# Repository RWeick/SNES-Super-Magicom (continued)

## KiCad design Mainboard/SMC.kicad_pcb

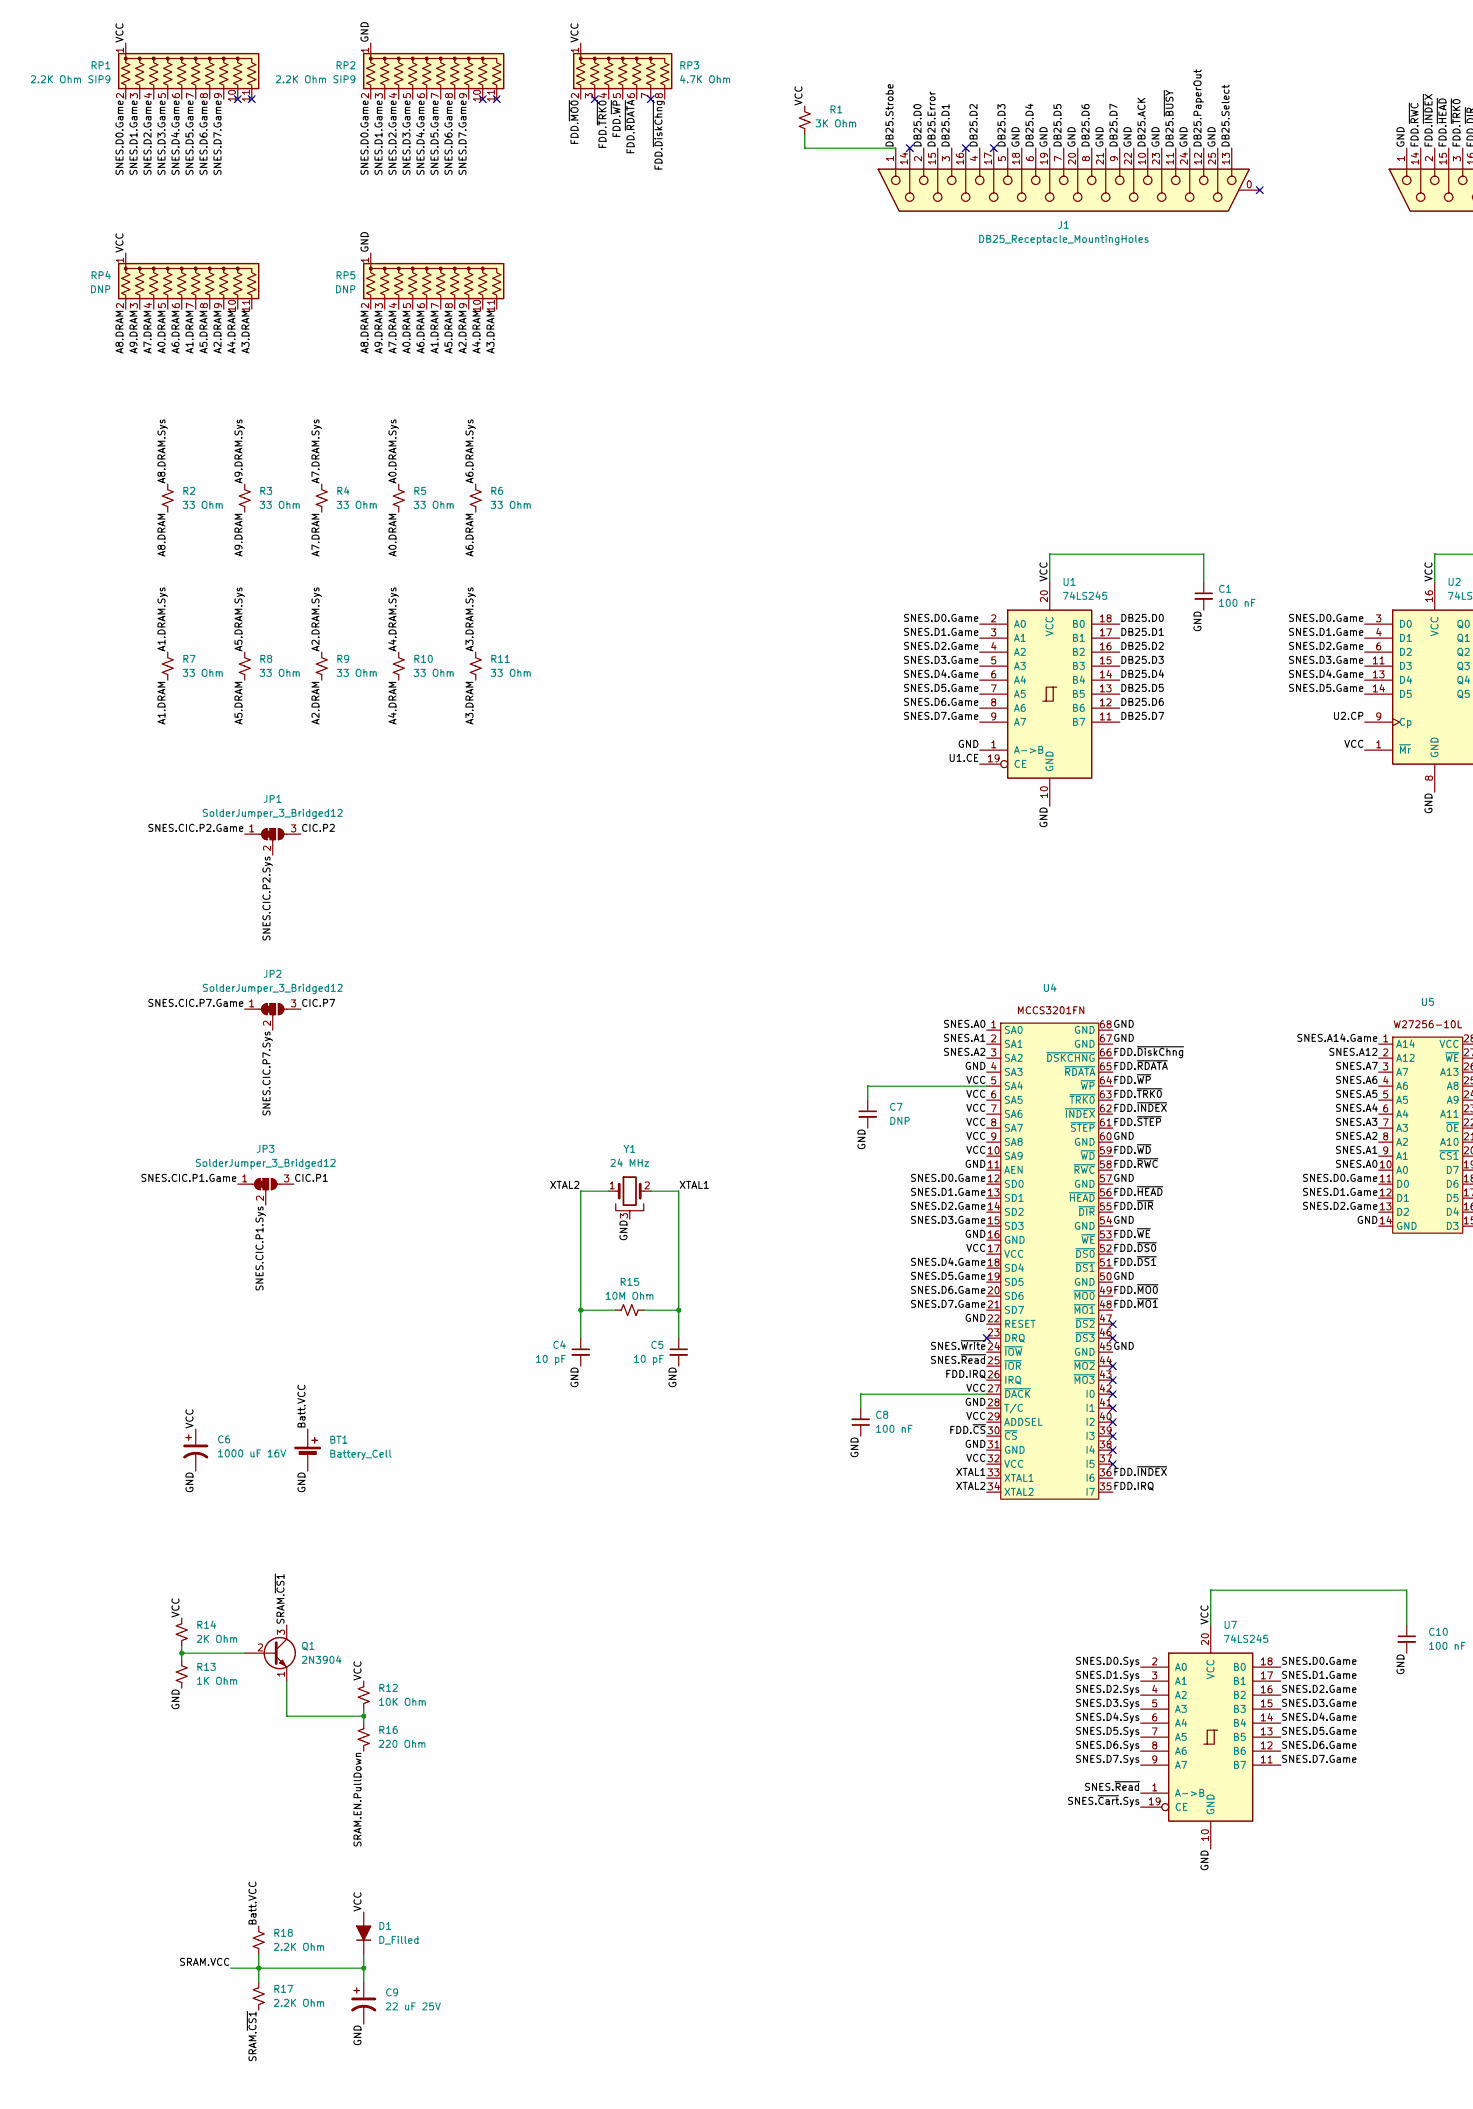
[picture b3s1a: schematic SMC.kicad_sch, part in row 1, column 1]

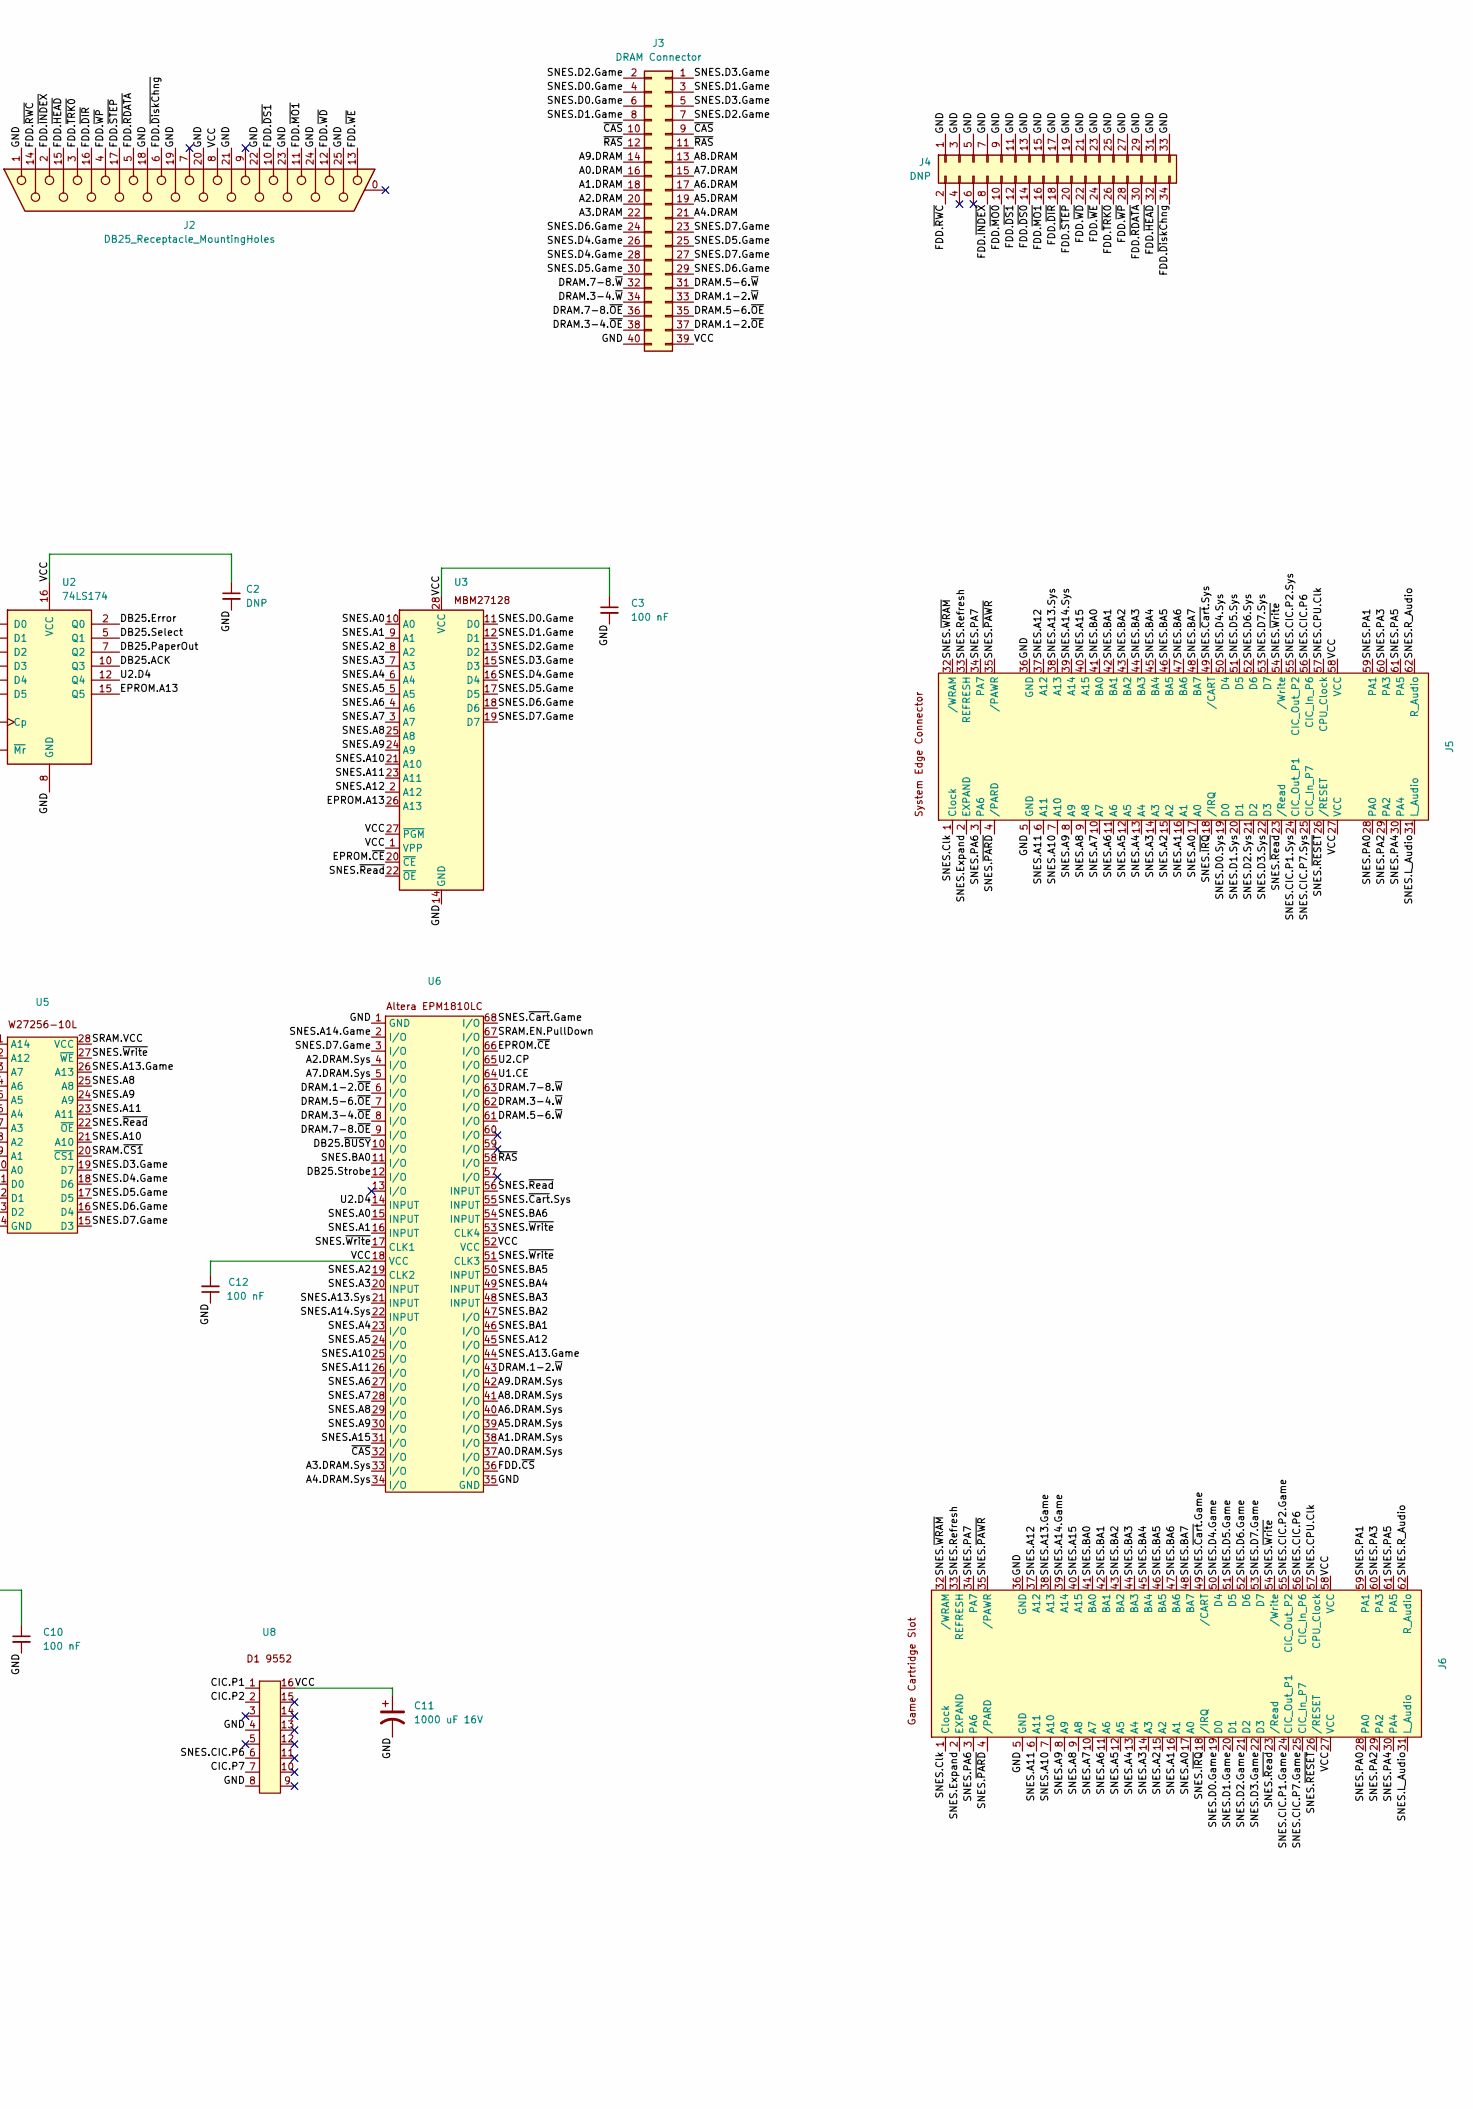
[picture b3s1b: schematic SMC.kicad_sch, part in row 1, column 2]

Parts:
BT1: Battery_Cell; Battery
C1, C3, C8, C10, C12: 100 nF; C_Disc_D4.3mm_W1.9mm_P5.00mm
C2, C7: DNP; C_Disc_D4.3mm_W1.9mm_P5.00mm
C4, C5: 10 pF; C_Disc_D4.3mm_W1.9mm_P5.00mm
C6, C11: 1000 uF 16V; C_Disc_D4.3mm_W1.9mm_P5.00mm
C9: 22 uF 25V; C_Disc_D4.3mm_W1.9mm_P5.00mm
D1: D_Filled; D_DO-15_P10.16mm_Horizontal
J1, J2: DB25_Receptacle_MountingHoles; DSUB-25_Female_Horizontal_P2.77x2.84mm_EdgePinOffset4.94mm_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
J3: DRAM Connector; PinHeader_2x20_P2.54mm_Vertical
J4: DNP; PinHeader_2x17_P2.54mm_Vertical
J5: SNES Connector Slot
J6: SNES Cartridge Slot
JP1, JP2, JP3: SolderJumper_3_Bridged12; SolderJumper-3_P1.3mm_Open_RoundedPad1.0x1.5mm_NumberLabels
Q1: 2N3904; TO-92_Wide
R1: 3K Ohm; R_Axial_DIN0207_L6.3mm_D2.5mm_P10.16mm_Horizontal
R2, R3, R4, R5, R6, R7, R8, R9, R10, R11: 33 Ohm; R_Axial_DIN0207_L6.3mm_D2.5mm_P10.16mm_Horizontal
R12: 10K Ohm; R_Axial_DIN0207_L6.3mm_D2.5mm_P10.16mm_Horizontal
R13: 1K Ohm; R_Axial_DIN0207_L6.3mm_D2.5mm_P10.16mm_Horizontal
R14: 2K Ohm; R_Axial_DIN0207_L6.3mm_D2.5mm_P10.16mm_Horizontal
R15: 10M Ohm; R_Axial_DIN0207_L6.3mm_D2.5mm_P10.16mm_Horizontal
R16: 220 Ohm; R_Axial_DIN0207_L6.3mm_D2.5mm_P10.16mm_Horizontal
R17, R18: 2.2K Ohm; R_Axial_DIN0207_L6.3mm_D2.5mm_P10.16mm_Horizontal
RP1, RP2: 2.2K Ohm SIP9; PinHeader_1x11_P2.54mm_Vertical
RP3: 4.7K Ohm; PinHeader_1x08_P2.54mm_Vertical
RP4, RP5: DNP; PinHeader_1x11_P2.54mm_Vertical
U1, U7: 74LS245; DIP-20_W7.62mm
U2: 74LS174; DIP-16_W7.62mm
U3: 27128; DIP-28_W15.24mm
U4, U6: PLCC-68_THT-Socket
U5: DIP-28_W15.24mm
U8: DIP-16_W7.62mm
Y1: 24 MHz; Crystal_HC18-U_Horizontal_1EP_style2

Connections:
/A0.DRAM: J3.16, R5.1, RP4.5 (R4), RP5.5 (R4)
/A0.DRAM.Sys: R5.2, U6.37 (I/O)
/A1.DRAM: J3.18, R7.1, RP4.7 (R6), RP5.7 (R6)
/A1.DRAM.Sys: R7.2, U6.38 (I/O)
/A2.DRAM: J3.20, R9.1, RP4.9 (R8), RP5.9 (R8)
/A2.DRAM.Sys: R9.2, U6.4 (I/O)
/A3.DRAM: J3.22, R11.1, RP4.11 (R10), RP5.11 (R10)
/A3.DRAM.Sys: R11.2, U6.33 (I/O)
/A4.DRAM: J3.21, R10.1, RP4.10 (R9), RP5.10 (R9)
/A4.DRAM.Sys: R10.2, U6.34 (I/O)
/A5.DRAM: J3.19, R8.1, RP4.8 (R7), RP5.8 (R7)
/A5.DRAM.Sys: R8.2, U6.39 (I/O)
/A6.DRAM: J3.17, R6.1, RP4.6 (R5), RP5.6 (R5)
/A6.DRAM.Sys: R6.2, U6.40 (I/O)
/A7.DRAM: J3.15, R4.1, RP4.4 (R3), RP5.4 (R3)
/A7.DRAM.Sys: R4.2, U6.5 (I/O)
/A8.DRAM: J3.13, R2.1, RP4.2 (R1), RP5.2 (R1)
/A8.DRAM.Sys: R2.2, U6.41 (I/O)
/A9.DRAM: J3.14, R3.1, RP4.3 (R2), RP5.3 (R2)
/A9.DRAM.Sys: R3.2, U6.42 (I/O)
/Batt.VCC: BT1.1 (+), R18.2
/CIC.P1: JP3.3 (B), U8.1
/CIC.P2: JP1.3 (B), U8.2
/CIC.P7: JP2.3 (B), U8.7
/DB25.ACK: J1.10, U2.10 (Q3)
/DB25.D0: J1.2, U1.18 (B0)
/DB25.D1: J1.3, U1.17 (B1)
/DB25.D2: J1.4, U1.16 (B2)
/DB25.D3: J1.5, U1.15 (B3)
/DB25.D4: J1.6, U1.14 (B4)
/DB25.D5: J1.7, U1.13 (B5)
/DB25.D6: J1.8, U1.12 (B6)
/DB25.D7: J1.9, U1.11 (B7)
/DB25.Error: J1.15, U2.2 (Q0)
/DB25.PaperOut: J1.12, U2.7 (Q2)
/DB25.Select: J1.13, U2.5 (Q1)
/DB25.Strobe: J1.1, R1.2, U6.12 (I/O)
/DB25.~BUSY: J1.11, U6.10 (I/O)
/DRAM.1-2.~OE: J3.37, U6.6 (I/O)
/DRAM.1-2.~W: J3.33, U6.43 (I/O)
/DRAM.3-4.~OE: J3.38, U6.8 (I/O)
/DRAM.3-4.~W: J3.34, U6.62 (I/O)
/DRAM.5-6.~OE: J3.35, U6.7 (I/O)
/DRAM.5-6.~W: J3.31, U6.61 (I/O)
/DRAM.7-8.~OE: J3.36, U6.9 (I/O)
/DRAM.7-8.~W: J3.32, U6.63 (I/O)
/EPROM.A13: U2.15 (Q5), U3.26 (A13)
/EPROM.~CE: U3.20 (~CE), U6.66 (I/O)
/FDD.IRQ: U4.26 (IRQ), U4.35 (I7)
/FDD.~CS: U4.30 (~CS), U6.36 (I/O)
/FDD.~DIR: J2.16, J4.18, U4.55 (~DIR)
/FDD.~DS0: J4.14, U4.52 (~DS0)
/FDD.~DS1: J2.10, J4.12, U4.51 (~DS1)
/FDD.~DiskChng: J2.6, J4.34, RP3.8 (R7), U4.66 (~DSKCHNG)
/FDD.~HEAD: J2.15, J4.32, U4.56 (~HEAD)
/FDD.~INDEX: J2.2, J4.8, U4.36 (I6), U4.62 (~INDEX)
/FDD.~MO0: J4.10, RP3.2 (R1), U4.49 (~MO0)
/FDD.~MO1: J2.11, J4.16, U4.48 (~MO1)
/FDD.~RDATA: J2.5, J4.30, RP3.6 (R5), U4.65 (~RDATA)
/FDD.~RWC: J2.14, J4.2, U4.58 (~RWC)
/FDD.~STEP: J2.17, J4.20, U4.61 (~STEP)
/FDD.~TRK0: J2.3, J4.26, RP3.4 (R3), U4.63 (~TRK0)
/FDD.~WD: J2.12, J4.22, U4.59 (~WD)
/FDD.~WE: J2.13, J4.24, U4.53 (~WE)
/FDD.~WP: J2.4, J4.28, RP3.5 (R4), U4.64 (~WP)
/GND: BT1.2 (-), C1.2, C2.2, C3.2, C4.2, C5.2, C6.2, C7.2, C8.1, C9.2, C10.2, C11.2, C12.1, J1.18, J1.19, J1.20, J1.21, J1.22, J1.23, J1.24, J1.25, J2.1, J2.18, J2.19, J2.20, J2.21, J2.22, J2.23, J2.24, J2.25, J3.40, J4.1, J4.3, J4.5, J4.7, J4.9, J4.11, J4.13, J4.15, J4.17, J4.19, J4.21, J4.23, J4.25, J4.27, J4.29, J4.31, J4.33, J5.5 (GND), J5.36 (GND), J6.5 (GND), J6.36 (GND), R13.1, RP2.1 (common), RP5.1 (common), U1.1 (A->B), U1.10 (GND), U2.8 (GND), U3.14 (GND), U4.4 (SA3), U4.11 (AEN), U4.16 (GND), U4.22 (RESET), U4.28 (T/C), U4.31 (GND), U4.45 (GND), U4.50 (GND), U4.54 (GND), U4.57 (GND), U4.60 (GND), U4.67 (GND), U4.68 (GND), U5.14 (GND), U6.1 (GND), U6.35 (GND), U7.10 (GND), U8.4, U8.8, Y1.3
/SNES.A0: J5.17 (A0), J6.17 (A0), U3.10 (A0), U4.1 (SA0), U5.10 (A0), U6.15 (INPUT)
/SNES.A1: J5.16 (A1), J6.16 (A1), U3.9 (A1), U4.2 (SA1), U5.9 (A1), U6.16 (INPUT)
/SNES.A2: J5.15 (A2), J6.15 (A2), U3.8 (A2), U4.3 (SA2), U5.8 (A2), U6.19 (CLK2)
/SNES.A3: J5.14 (A3), J6.14 (A3), U3.7 (A3), U5.7 (A3), U6.20 (INPUT)
/SNES.A4: J5.13 (A4), J6.13 (A4), U3.6 (A4), U5.6 (A4), U6.23 (I/O)
/SNES.A5: J5.12 (A5), J6.12 (A5), U3.5 (A5), U5.5 (A5), U6.24 (I/O)
/SNES.A6: J5.11 (A6), J6.11 (A6), U3.4 (A6), U5.4 (A6), U6.27 (I/O)
/SNES.A7: J5.10 (A7), J6.10 (A7), U3.3 (A7), U5.3 (A7), U6.28 (I/O)
/SNES.A8: J5.9 (A8), J6.9 (A8), U3.25 (A8), U5.25 (A8), U6.29 (I/O)
/SNES.A9: J5.8 (A9), J6.8 (A9), U3.24 (A9), U5.24 (A9), U6.30 (I/O)
/SNES.A10: J5.7 (A10), J6.7 (A10), U3.21 (A10), U5.21 (A10), U6.25 (I/O)
/SNES.A11: J5.6 (A11), J6.6 (A11), U3.23 (A11), U5.23 (A11), U6.26 (I/O)
/SNES.A12: J5.37 (A12), J6.37 (A12), U3.2 (A12), U5.2 (A12), U6.45 (I/O)
/SNES.A13.Game: J6.38 (A13), U5.26 (A13), U6.44 (I/O)
/SNES.A13.Sys: J5.38 (A13), U6.21 (INPUT)
/SNES.A14.Game: J6.39 (A14), U5.1 (A14), U6.2 (I/O)
/SNES.A14.Sys: J5.39 (A14), U6.22 (INPUT)
/SNES.A15: J5.40 (A15), J6.40 (A15), U6.31 (I/O)
/SNES.BA0: J5.41 (BA0), J6.41 (BA0), U6.11 (I/O)
/SNES.BA1: J5.42 (BA1), J6.42 (BA1), U6.46 (I/O)
/SNES.BA2: J5.43 (BA2), J6.43 (BA2), U6.47 (I/O)
/SNES.BA3: J5.44 (BA3), J6.44 (BA3), U6.48 (INPUT)
/SNES.BA4: J5.45 (BA4), J6.45 (BA4), U6.49 (INPUT)
/SNES.BA5: J5.46 (BA5), J6.46 (BA5), U6.50 (INPUT)
/SNES.BA6: J5.47 (BA6), J6.47 (BA6), U6.54 (INPUT)
/SNES.BA7: J5.48 (BA7), J6.48 (BA7)
/SNES.CIC.P1.Game: J6.24 (CIC_Out_P1), JP3.1 (A)
/SNES.CIC.P1.Sys: J5.24 (CIC_Out_P1), JP3.2 (C)
/SNES.CIC.P2.Game: J6.55 (CIC_Out_P2), JP1.1 (A)
/SNES.CIC.P2.Sys: J5.55 (CIC_Out_P2), JP1.2 (C)
/SNES.CIC.P6: J5.56 (CIC_In_P6), J6.56 (CIC_In_P6), U8.6
/SNES.CIC.P7.Game: J6.25 (CIC_In_P7), JP2.1 (A)
/SNES.CIC.P7.Sys: J5.25 (CIC_In_P7), JP2.2 (C)
/SNES.CPU.Clk: J5.57 (CPU_Clock), J6.57 (CPU_Clock)
/SNES.Clk: J5.1 (Clock), J6.1 (Clock)
/SNES.D0.Game: J3.4, J3.6, J6.19 (D0), RP1.2 (R1), RP2.2 (R1), U1.2 (A0), U2.3 (D0), U3.11 (D0), U4.12 (SD0), U5.11 (D0), U7.18 (B0)
/SNES.D0.Sys: J5.19 (D0), U7.2 (A0)
/SNES.D1.Game: J3.3, J3.8, J6.20 (D1), RP1.3 (R2), RP2.3 (R2), U1.3 (A1), U2.4 (D1), U3.12 (D1), U4.13 (SD1), U5.12 (D1), U7.17 (B1)
/SNES.D1.Sys: J5.20 (D1), U7.3 (A1)
/SNES.D2.Game: J3.2, J3.7, J6.21 (D2), RP1.4 (R3), RP2.4 (R3), U1.4 (A2), U2.6 (D2), U3.13 (D2), U4.14 (SD2), U5.13 (D2), U7.16 (B2)
/SNES.D2.Sys: J5.21 (D2), U7.4 (A2)
/SNES.D3.Game: J3.1, J3.5, J6.22 (D3), RP1.5 (R4), RP2.5 (R4), U1.5 (A3), U2.11 (D3), U3.15 (D3), U4.15 (SD3), U5.19 (D7), U7.15 (B3)
/SNES.D3.Sys: J5.22 (D3), U7.5 (A3)
/SNES.D4.Game: J3.26, J3.28, J6.50 (D4), RP1.6 (R5), RP2.6 (R5), U1.6 (A4), U2.13 (D4), U3.16 (D4), U4.18 (SD4), U5.18 (D6), U7.14 (B4)
/SNES.D4.Sys: J5.50 (D4), U7.6 (A4)
/SNES.D5.Game: J3.25, J3.30, J6.51 (D5), RP1.7 (R6), RP2.7 (R6), U1.7 (A5), U2.14 (D5), U3.17 (D5), U4.19 (SD5), U5.17 (D5), U7.13 (B5)
/SNES.D5.Sys: J5.51 (D5), U7.7 (A5)
/SNES.D6.Game: J3.24, J3.29, J6.52 (D6), RP1.8 (R7), RP2.8 (R7), U1.8 (A6), U3.18 (D6), U4.20 (SD6), U5.16 (D4), U7.12 (B6)
/SNES.D6.Sys: J5.52 (D6), U7.8 (A6)
/SNES.D7.Game: J3.23, J3.27, J6.53 (D7), RP1.9 (R8), RP2.9 (R8), U1.9 (A7), U3.19 (D7), U4.21 (SD7), U5.15 (D3), U6.3 (I/O), U7.11 (B7)
/SNES.D7.Sys: J5.53 (D7), U7.9 (A7)
/SNES.Expand: J5.2 (EXPAND), J6.2 (EXPAND)
/SNES.L_Audio: J5.31 (L_Audio), J6.31 (L_Audio)
/SNES.PA0: J5.28 (PA0), J6.28 (PA0)
/SNES.PA1: J5.59 (PA1), J6.59 (PA1)
/SNES.PA2: J5.29 (PA2), J6.29 (PA2)
/SNES.PA3: J5.60 (PA3), J6.60 (PA3)
/SNES.PA4: J5.30 (PA4), J6.30 (PA4)
/SNES.PA5: J5.61 (PA5), J6.61 (PA5)
/SNES.PA6: J5.3 (PA6), J6.3 (PA6)
/SNES.PA7: J5.34 (PA7), J6.34 (PA7)
/SNES.R_Audio: J5.62 (R_Audio), J6.62 (R_Audio)
/SNES.Refresh: J5.33 (REFRESH), J6.33 (REFRESH)
/SNES.~Cart.Game: J6.49 (/CART), U6.68 (I/O)
/SNES.~Cart.Sys: J5.49 (/CART), U6.55 (INPUT), U7.19 (CE)
/SNES.~IRQ: J5.18 (/IRQ), J6.18 (/IRQ)
/SNES.~PARD: J5.4 (/PARD), J6.4 (/PARD)
/SNES.~PAWR: J5.35 (/PAWR), J6.35 (/PAWR)
/SNES.~RESET: J5.26 (/RESET), J6.26 (/RESET)
/SNES.~Read: J5.23 (/Read), J6.23 (/Read), U3.22 (~OE), U4.25 (~IOR), U5.22 (~OE), U6.56 (INPUT), U7.1 (A->B)
/SNES.~WRAM: J5.32 (/WRAM), J6.32 (/WRAM)
/SNES.~Write: J5.54 (/Write), J6.54 (/Write), U4.24 (~IOW), U5.27 (~WE), U6.17 (CLK1), U6.51 (CLK3), U6.53 (CLK4)
/SRAM.EN.PullDown: R16.2, U6.67 (I/O)
/SRAM.VCC: C9.1, D1.1 (K), R17.1, R18.1, U5.28 (VCC)
/SRAM.~CS1: Q1.3 (C), R17.2, U5.20 (~CS1)
/U1.CE: U1.19 (CE), U6.64 (I/O)
/U2.CP: U2.9 (Cp), U6.65 (I/O)
/U2.D4: U2.12 (Q4), U6.14 (INPUT)
/VCC: C1.1, C2.1, C3.1, C6.1, C7.1, C8.2, C10.1, C11.1, C12.2, D1.2 (A), J2.8, J3.39, J5.27 (VCC), J5.58 (VCC), J6.27 (VCC), J6.58 (VCC), R1.1, R12.1, R14.1, RP1.1 (common), RP3.1 (common), RP4.1 (common), U1.20 (VCC), U2.1 (~Mr), U2.16 (VCC), U3.1 (VPP), U3.27 (~PGM), U3.28 (VCC), U4.5 (SA4), U4.6 (SA5), U4.7 (SA6), U4.8 (SA7), U4.9 (SA8), U4.10 (SA9), U4.17 (VCC), U4.27 (~DACK), U4.29 (ADDSEL), U4.32 (VCC), U6.18 (VCC), U6.52 (VCC), U7.20 (VCC), U8.16
/XTAL1: C5.1, R15.2, U4.33 (XTAL1), Y1.2
/XTAL2: C4.1, R15.1, U4.34 (XTAL2), Y1.1
/~CAS: J3.9, J3.10, U6.32 (I/O)
/~RAS: J3.11, J3.12, U6.58 (I/O)
unnamed: Q1.2 (B), R13.2, R14.2
unnamed: Q1.1 (E), R12.2, R16.1

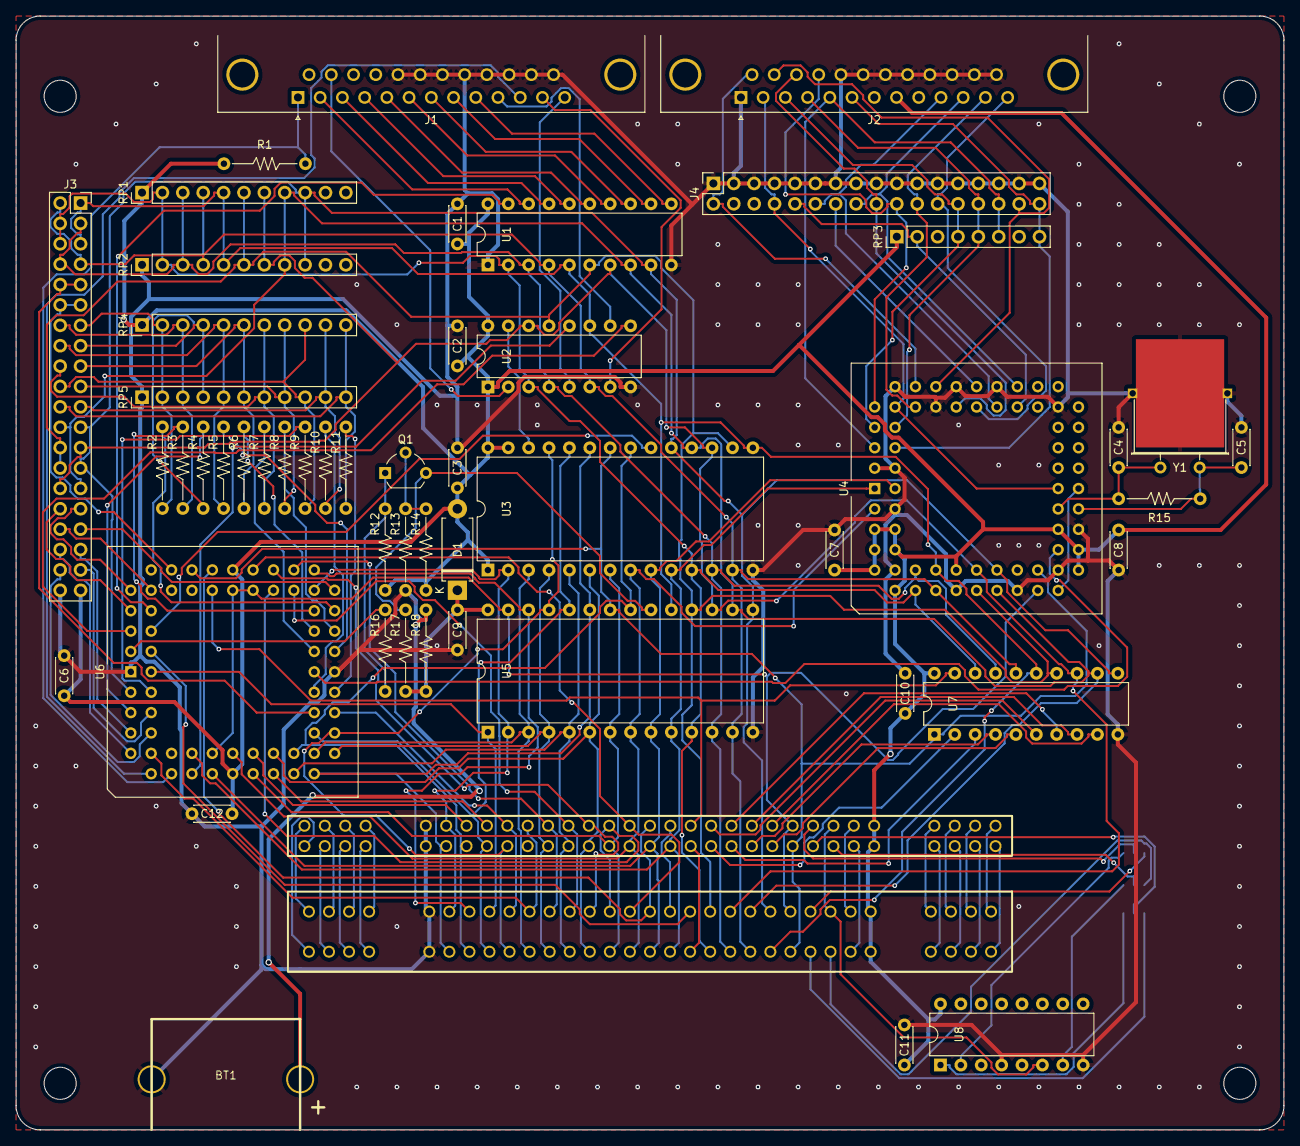
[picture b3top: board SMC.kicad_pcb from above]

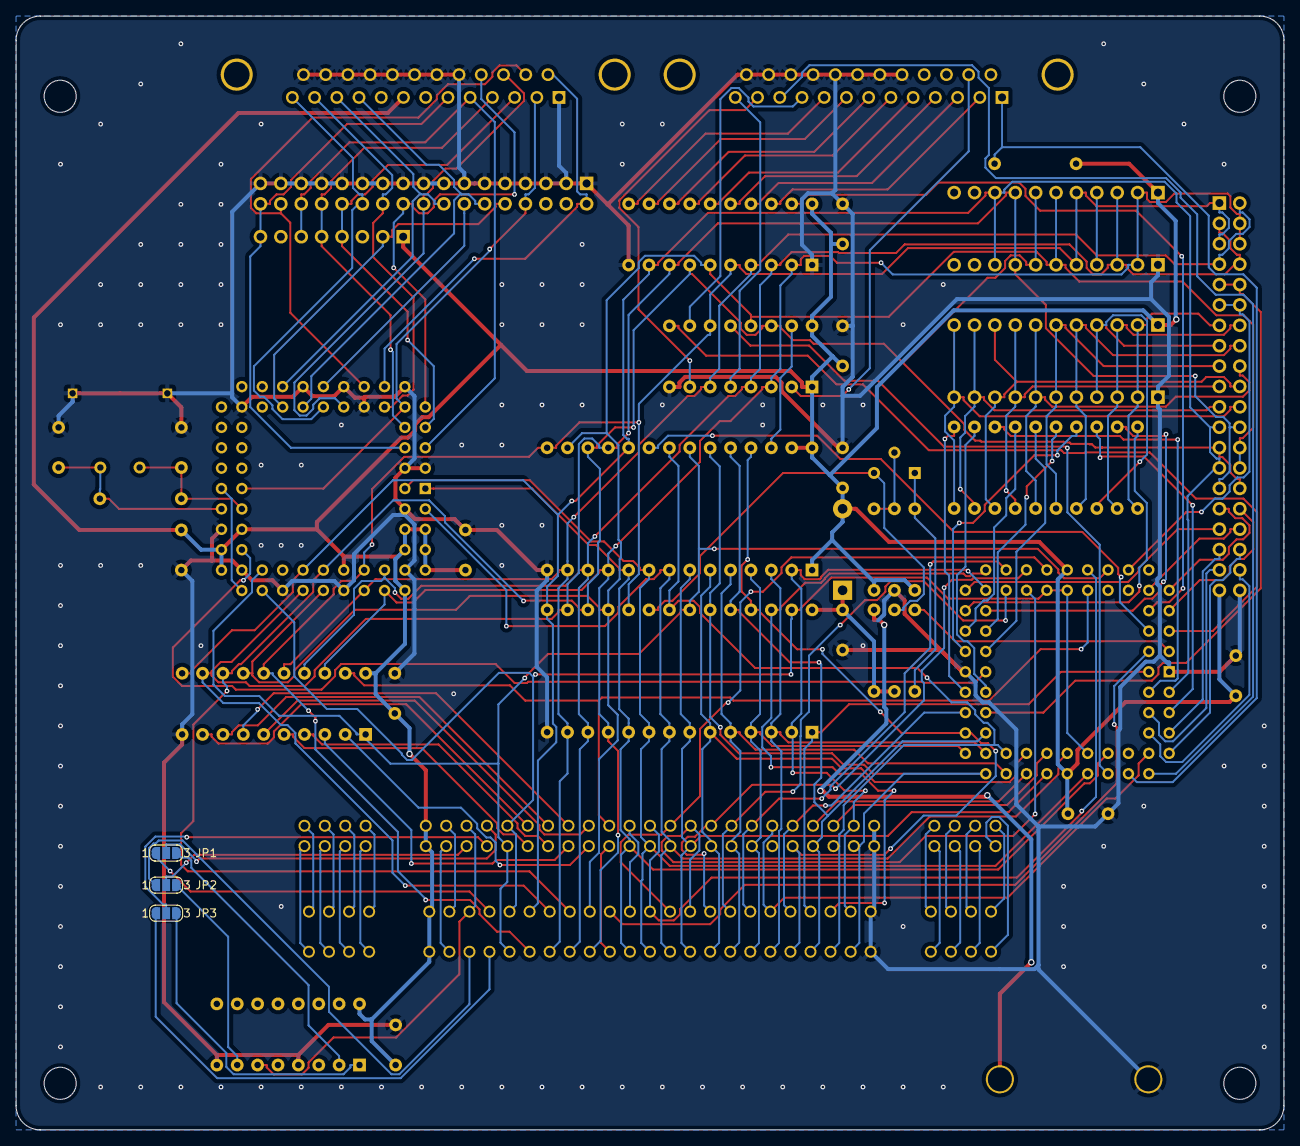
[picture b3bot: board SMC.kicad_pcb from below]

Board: 2 copper layers, 158.0 x 138.8 mm, 56 parts (3 on the bottom side), 151 nets.
